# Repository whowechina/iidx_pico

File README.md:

# IIDX Pico - Beatmania IIDX Style Mini Controller
[点这里可以切换到中文版](README_CN.md)

## Features
* Cool thin design.
* Many variants: IIDX Pico, IIDX Teeny, IIDX Jumbo and IIDX Itsy.
* Foldable with soft hinge.
* Now supports both Hall effect switches and mechanical switches.
* Customizable lights and effects.
* HID lights.
* IIDX Visa card holder.
* All source files open.

## Change Notes
* All IIDX Pico variants have been integrated into this repository for better management.
* The old IIDX Teeny repository has been archived and will be no longer updated.
* Old files have been moved to the Gen1Archive directory, but can also be found in the historical versions.

## Thanks
Thanks to many respectful guys/companies who made their tools or materials free or open source (KiCad, OnShape, InkScape, Raspberry things).

Special thanks to community projects and developers.
And also these projects:
* RP_Silicon_KiCad: https://github.com/HeadBoffin/RP_Silicon_KiCad
* Type-C: https://github.com/ai03-2725/Type-C.pretty
* Bluetooth for UM: https://github.com/987123879113/Esp32EntryModel

## My Other Projects
You can check out my other cool projects.

* Popn Pico: https://github.com/whowechina/popn_pico
* IIDX Pico: https://github.com/whowechina/iidx_pico
* Chu Pico: https://github.com/whowechina/chu_pico
* Mai Pico: https://github.com/whowechina/mai_pico
* Diva Pico: https://github.com/whowechina/diva_pico
* AIC Pico: https://github.com/whowechina/aic_pico
* Groove Pico: https://github.com/whowechina/groove_pico
* Geki Pico: https://github.com/whowechina/geki_pico
* Musec Pico: https://github.com/whowechina/musec_pico
* Ju Pico: https://github.com/whowechina/ju_pico
* Bishi Pico: https://github.com/whowechina/bishi_pico
* Nos Pico: https://github.com/whowechina/nos_pico
* Voltex Pico: https://github.com/whowechina/voltex_pico
* Chord Pico: https://github.com/whowechina/chord_pico
* Dance Pico: https://github.com/whowechina/dance_pico
* Arcade Pico: https://github.com/whowechina/arcade_pico

## **Disclaimer** ##
I made this project in my personal time with no financial benefit or sponsorship. I will continue to improve the project. I have done my best to ensure that everything is accurate and functional, there's always a chance that mistakes may occur. I cannot be held responsible for any loss of your time or money that may result from using this open source project. Thank you for your understanding.

## About the License
It's CC-NC. So DIY for yourself and for your friend, don't make money from it. And plagiarism that doesn’t even dare to mention the original author is not acceptable. Please note that pooling orders and group buying for raw materials is acceptable.Selling any leftover components at cost (without profit) is also acceptable.

If you're interested in buying from me, or for commercial use, please contact me (Discord, QQ group, Goofish).
* My Discord Invitation: https://discord.gg/M8f2PPQFEA
* QQ Group: 854535476
* Goofish: whowe12345

## HOW TO BUILD
### Turntable Materials
* 1x 5mm\*2mm magnet (must be radially magnetized).
* 1x 61804-2RS deep groove ball bearing (20x32x7mm), just choose the cheaper ones.
* 2x 6705-2RS (alternative) deep groove ball bearings (25x32x4mm) for IIDX Jumbo, less wobbling.
* 1x WS2812B LED strip. Go with ones with dense LED configurations. I recommend 80 LEDs per meter or higher for IIDX Pico and IIDX Jumbo; 120 LEDs per meter or higher for IIDX Teeny;
* 1x M2.5*6 screw and hex nut, to fix disc seat, magnet seat and bearing together.
* 4x M3*8mm screws, to fix bearing seat to the base.
* 4x M3*12mm screws, for the disc. 
* 2x M3*8mm screws and hex nuts, for the banner.
* 1x Custom cut black acrylic disc, 3mm thickness for IIDX Pico and IIDX Jumbo.
* Some 10mm non slip self-adhesive silicon pads (also for Keyboard).
* Silicone tube, inner diameter 25mm, outer diameter 27mm, serves as a hinge.
* Some soft ribbon cable with 7 wires, silicone 28AWG is recommended.
* Some acetate cloth tape helps to fix the wires.

### PCB and Keyboard Materials
* 1x Raspberry Pi Pico (or Pi Pico W if you want Bluetooth). If you're building the Itsy, use the "Supermini RP2040 Zero" module instead - it looks like the RP2040 Zero, but has components only on top side.  
  https://www.raspberrypi.com/products/raspberry-pi-pico
* 11x Kailh Choc v1 or v2 key switches, I suggest using linear switches for the 7 main buttons.  
  https://www.kailhswitch.com/mechanical-keyboard-switches/low-profile-key-switches/burnt-orange-switch.html  
  https://www.kailhswitch.com/mechanical-keyboard-switches/key-switches/kailh-low-profile-switch-choc-v2.html
* 7x Kailh 2.0U low-profile stabilizers.  
  https://chosfox.com/products/kailh-1350-choc-switch-6-25u-stabilizer-set
* 2x Panasonic EVQP1K05M square tactile switches for IIDX Pico and IIDX Jumbo.  
  https://www3.panasonic.biz/ac/e/dl/catalog/index.jsp?series_cd=3473&part_no=EVQP1K05M
* 6x Panasonic EVQP1K05M or ALPS SKPMAPE010 square tactile switches for IIDX Teeny.  
  https://www3.panasonic.biz/ac/e/dl/catalog/index.jsp?series_cd=3473&part_no=EVQP1K05M  
  https://tech.alpsalpine.com/e/products/detail/SKPMAPE010/
* 1x USB Type-C socket (918-418K2023S40001 or KH-TYPE-C-16P)
* 1x AS5600 (SOP8), MT6701CT-STD (SOP8), or TMAG5273 (SOT23-6) hall angular sensor chip. For MT6701, trim pin 8 (Z/CSN) if JP1 is not present on the PCB; for AS5600, solder bridge JP1 if it is present.
* RGB LEDs
  * IIDX Pico and IIDX Jumbo (nicer light effect version)
    * 28x WS2812B-1516 or WS2812B-2020 for main buttons, pinout should be exactly like this:  
      
    * 4x WS2812B-3528 (or WS2812B-2835), for AUX buttons.
  * IIDX Pico and IIDX Jumbo (easier soldering version)
    * 11x WS2812B-3528 (or WS2812B-2835), forget about ridiculously tiny 28x LEDs.
  * IIDX Teeny
    * 18 WS2812B-3528 (or WS2812B-2835).
* 4x 0603 5.1kohm resistors for USB and I2C.
* 6x 0603 0.1uF capacitors for IIDX Pico and IIDX Jumbo, 4x for IIDX Teeny.
* 4x Kailh low-profile keycaps for IIDX Pico and IIDX Jumbo.
* 4x M3*8mm screws and hex nuts to fix parts together.

### If you want to build Hall Effect version
* WS2812B-3528 per switch is no longer an option. Because it conflicts with the pinout.
* 1x ADG708BRUZ, 8 to 1 analog switch, in TSSOP-16 (U4).
* 1x LP5907MFX-4.5 or TPS7A2042PDBVR LDO, in SOT23-5 (U6), see next line.
* 1x LM4040 shunt voltage reference, get one with 2.0\~2.1V (for 4.2V LDO) or 2.2\~2.5V (for 4.5V LDO) reference voltage, in SOT23-3 (U5).
* 7x SS49E or compatible linear Hall Effect sensors, in SOT23-3 (H1-H7).
* 1x 10ohm resistor, 0603 (R5) and leave R6 absent.
* 1x 3.3V Zener diode, in SOD-123 or SOD-123F, such as BZT52H-C3V3 (Z1).
* 7x low profile magnetic switches, Gateron/NuPhy Jade Mini or Jade Pro Mini, Kailh Star Magnetic Mini, or compatible ones. (SW1-SW7).
* Some more 0.1uF capacitors. (All remaining capacitor positions).
* This shows the soldering for Hall Effect version.  

### Step 1 - Buy
* Main PCB  
  Just go [JLC](https://jlcpcb.com/) or some other PCB vendor you like and make the order. Make sure the board thickness is **1.2mm**, it's very important!
* Acrylic disc for IIDX Pico and IIDX Jumbo.  
  Find a vendor to cut a 3mm thick black acrylic using corresponding DXF file.  
  You can 3D print a turntable disc, but it is prone to heat deformation.

### Step 2 - 3D Print
#### Keyboard
For following prints, FDM, PLA, 0.4 nozzle, 0.2mm layer.
* Keyboard base ("Keyboard Base *.stl), PLA/PETG transparent, 2 to 3 walls.
* Keyboard panel ("Keyboard Panel.stl"), PLA/PETG transparent, 2 to 3 walls. Please render the panel art and text (height 3mm+) in black if you have multi-color printing system.

#### Turntable 
For following prints, FDM, PLA, 0.4 nozzle, 0.2mm layer, 3 to 4 walls.
* Base ("Turntable \* - Base.stl"), 20-40% infill.
* Bearing seat ("Turntable - Bearing Seat"), 40% to 60% infill.
* Magnet seat ("Turntable - Magnet Seat"), 40% to 60% infill.
* Disc seat ("Turntable - Disc Seat"), 40% to 60% infill.
* For IIDX Teeny only, the disc ("Turntable Teeny - Disc"), 80%+ infill, use a textured PEI bed and concentric pattern for a better surface.
* Banner ("Turntable * - Banner"), 20-40% infill. You can render the text in black if you have multi-color printing system.
* NOTE: IIDX Jumbo with 2 bearings is abbreviated as "Jumbo 2B" in the file name.

#### Button keycaps
* Keycap ("Keycap *.stl", choose the one matches your build), resin printing is recommended, but FDM can work in a pinch.

### Step 3 - Soldering and Assembly Tips
* Keyboard
  * It's very easy to miss two USB pins of the Raspberry Pico Pi, it's at the other side. It's difficult to solder as you may leave air bubbles in the soldering hole. Trick is to use sharpest iron tip, slowly apply solder wire.  
    
  * As long as you have Pi Pico soldered, you can upload firmware and test the board. Please test frequently during the soldering and assembly process.
  * There are two small sensor boards on the main PCB, one for AS5600, the other for TMAG5273. You only need one. After a successful test, you can snap it off for turntable assembly.
  * This gamepad test page can be used for testing. You can move a screwdriver bit on top of the AS5600 or TMAG5273 to see the axis movement.  
    https://greggman.github.io/html5-gamepad-test/
  * Install the low-profile stabilizers.  
    https://docs.keeb.io/choc-stabs  
    A little trick here. Since the PCB footprint is made to support both choc v1 and v2, that leaves some wobble space for choc v1 and making alignment more difficult. So leave the key switch unsoldered, when the stabilizer, the key switch and the keycap are all in place, push the keycap down and then solder the key switch. This way the key switch will be aligned to the stabilizers better.

* Turntable
  * Assembly is pretty straightforward.  

  * Sensor board is stuck to the base using some thin double-sided tape.
  * For IIDX Jumbo, two 6705-2RS bearings are stacked together.
  * Bearings are originally with very low friction, if you need more resistance, you can add some medium viscosity damping grease, but don't add too much. "2RS" in the bearing model means it's rubber sealed, it's easy to open the rubber seal and add grease.
  * RGB LED strip is stuck to the circular LED wall, both winding directions work.  
  * The 7-wire ribbon cable is for both the RGB LED and the sensor board, 3 for RGB LED, 4 for the sensor board.  
    
  * Silicone tube is to connect the turntable and the keyboard. Ribbon cable needs to go through the tube. You need a 7mm or 8mm hole punch to make holes on the silicone tube, to match the hooks at both turntable base and the keyboard sides.

### Notes on Hall Effect version
* For Kailh Star Mini, you need to use 704 RTV silicone adhesive to secure the magnetic switch to the PCB, to prevent it wobbling.
* Calibration must be done in the command line interface.
* Travel distance for triggering and reset can be configured only in the command line interface. They're stored in profile, which means, you can switch between different profiles and have different triggering settings for each profile.

### Firmware
* The UF2 file is in the `Production\Firmware` folder. IIDX Pico/Teeny/Jumbo share the same IIDX Pico firmware.
* For the new build, hold the BOOTSEL button while connect the USB to a PC, there will be a disk named "RPI-RP2" showed up. Drag the UF2 firmware binary file into it and that's it. There's a small hole at the back side of the keyboard, it is facing right to the BOOTSEL button.
* If it is already running my IIDX firmware, hold two small AUX buttons together will do the same as the BOOTSEL button.
* You need to setup your turntable LED strip first, check the manual for the SETUP mode.
* Hold E1+E2 while powering on to start Bluetooth pairing on Pico W.
* You can set the brightness, turntable LED theme, button LED theme.
* [Nice Looking Manual Here](doc/IIDX_Pico_Manual.pdf)  

### Tools I Made
* Gamepad test - You can use it to check if all buttons and axes are working correctly.   
  https://whowechina.github.io/iidx_pico/Tools/gamepad_test.html
* Command-line tool - You can access controller's built-in CLI port using this tool.  
  https://whowechina.github.io/iidx_pico/Tools/cli_tool.html

### Bonus - IIDX Visa Card Holder

* IIDX Visa card holder is a bonus design for IIDX Pico. It can be used to hold your credit card sized arcade cards.
* Print the base and the panel, assign different color for the pattern and text on the panel. `_insert` means it's the heat-set insert version. `_flat` means it's for flat head (countersunk) screws. Transparent material is recommended.
* If you choose the `_insert` version, use 4x M1.2\*1.5mm\*2mm (thread size\*length\*diameter) heat-set inserts on base part.
* 4x M1.2\*3mm screws to fix the panel and the base together. If you choose the `_flat` version, use M1.2\*3mm flat head screws.

## CAD Source File
I'm using OnShape free subscription. It's powerful but it can't archive original designs to local, so I can only share the link here. STL/DXF/DWG files are exported from this online document.  
https://cad.onshape.com/documents/ed99bfa5b4aec5d3ea6e6ed6/w/9a87f8b714078597b4ef5e3c/e/2e27bace5a421a921473c027

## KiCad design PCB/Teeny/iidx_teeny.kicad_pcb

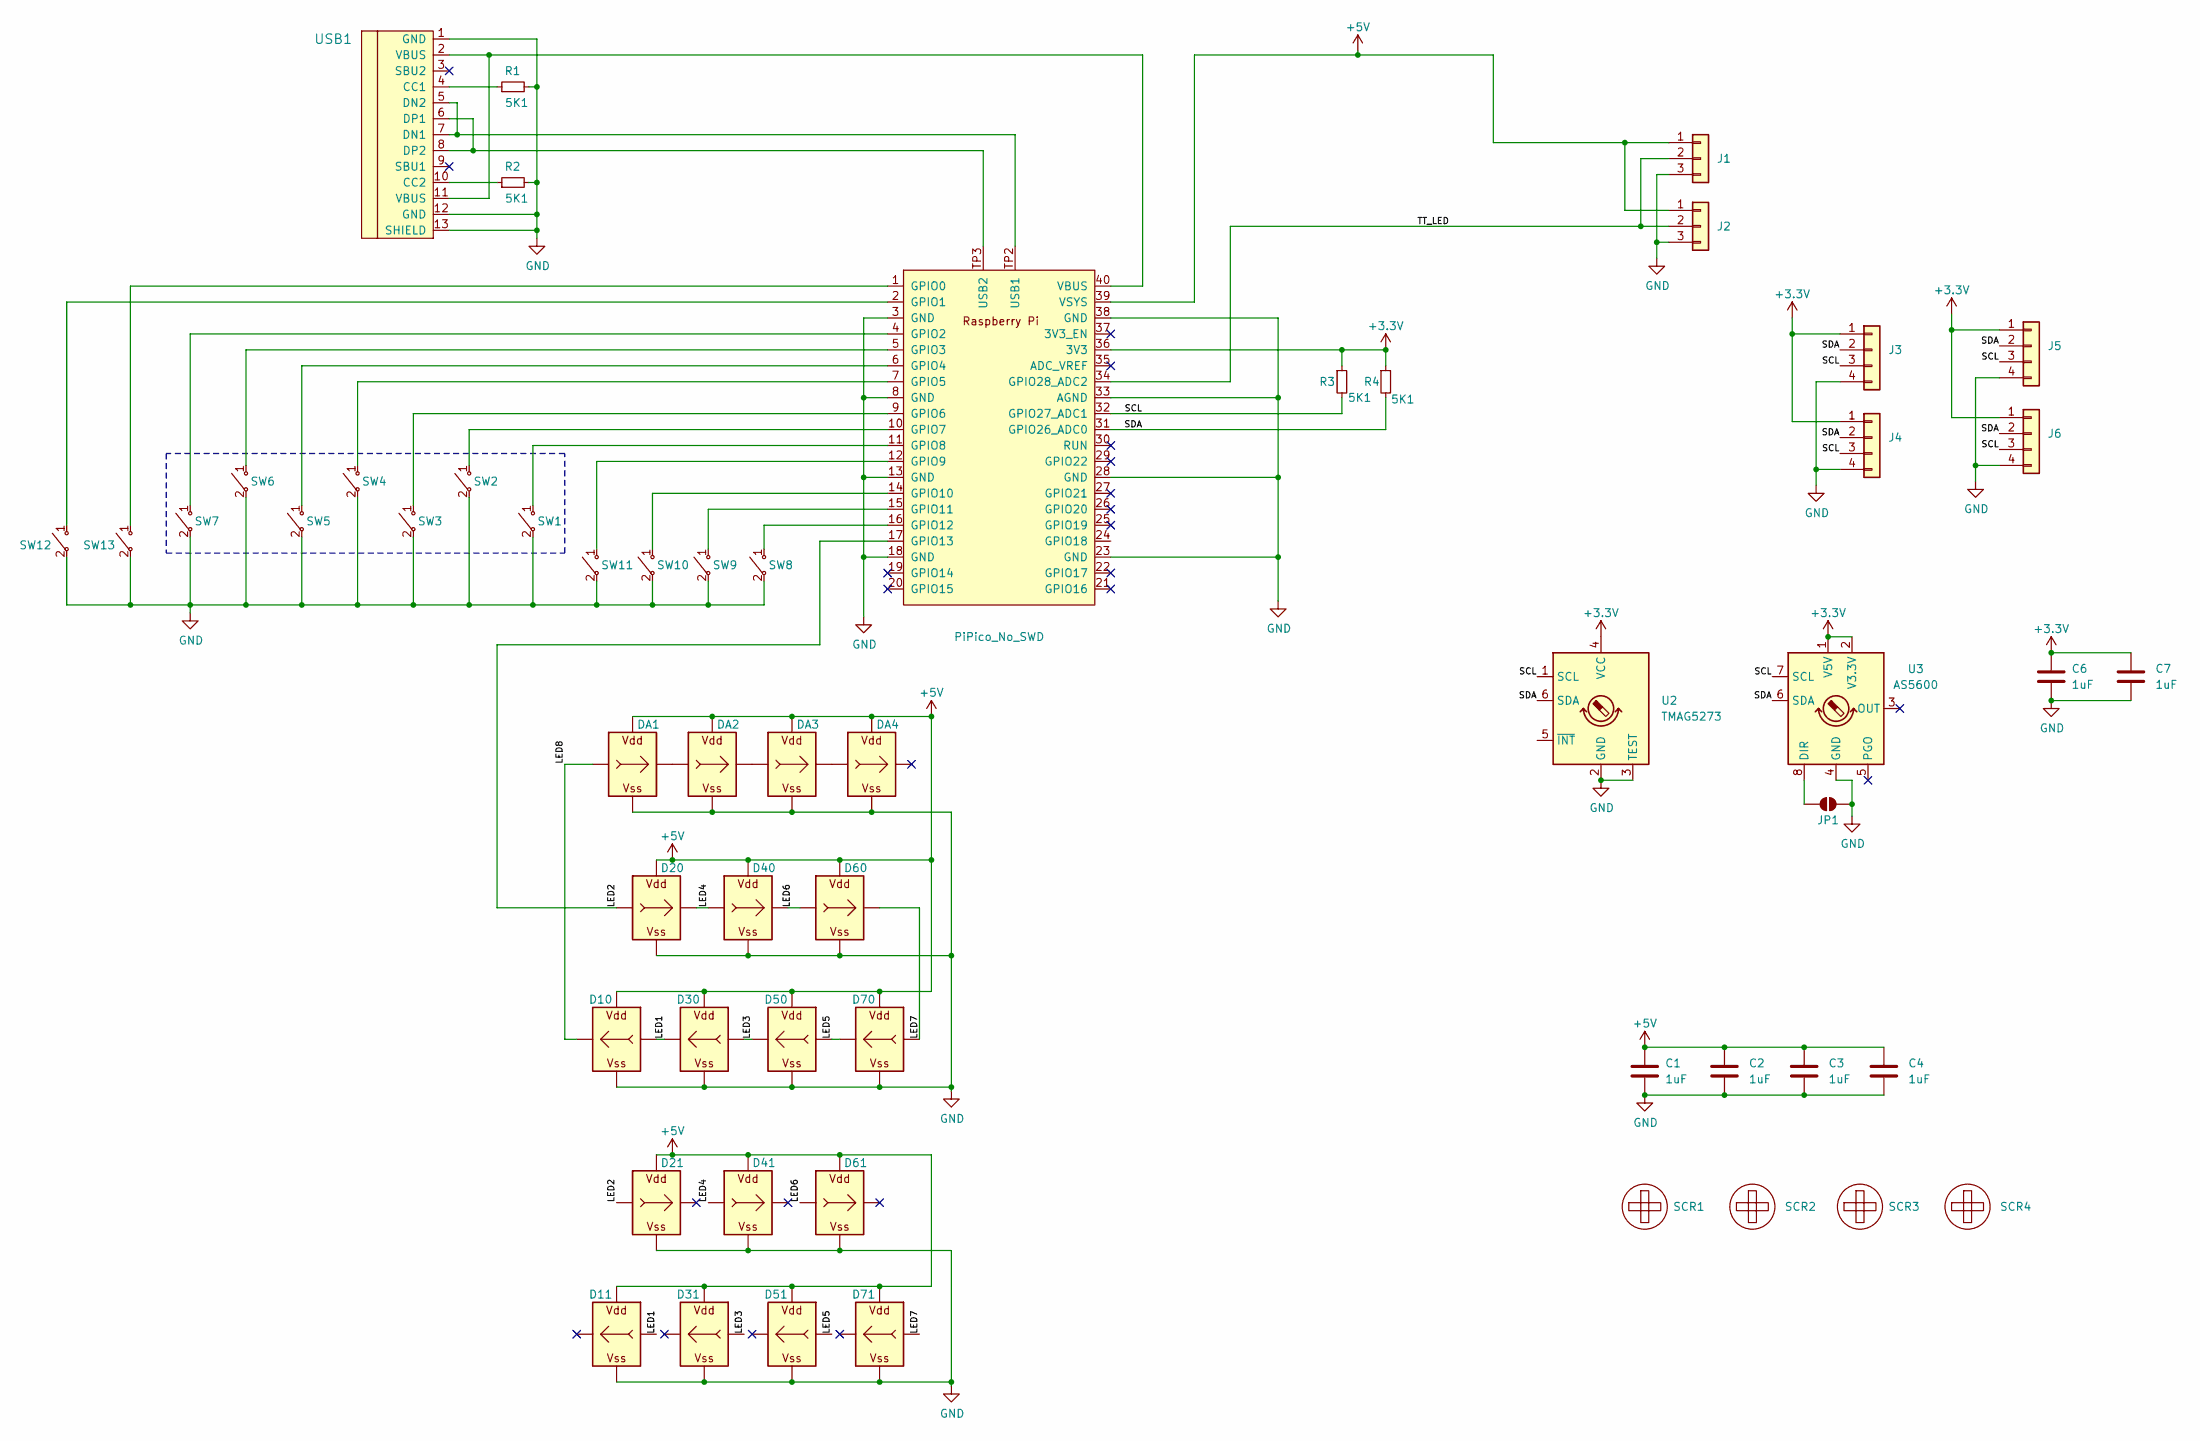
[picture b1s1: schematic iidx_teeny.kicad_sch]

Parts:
C1, C2, C3, C4, C6, C7: 1uF; C_0603_1608Metric_Pad1.08x0.95mm_HandSolder
D10, D11, D20, D21, D30, D31, D40, D41, D50, D51, D60, D61, D70, D71: WS2812B_Unified; WS2812B-2835
DA1, DA2, DA3, DA4: WS2812B_Unified; WS2812B-2835
J1, J2: RGB; SH1.0_3P_Solder_Combo
J3, J4: Spin; SH1.0_4P_Solder_Combo
J5, J6: Spin; P2.0_4P_Solder
JP1: DIR; SolderJumper-2_P1.3mm_Open_RoundedPad1.0x1.5mm
R1, R2, R3, R4: 5K1; R_0603_1608Metric_Pad0.98x0.95mm_HandSolder; LCSC C23186
SCR1, SCR2, SCR3, SCR4: ScrewHole; MountingHole_3.2mm_M3
SW1, SW2, SW3, SW4, SW5, SW6, SW7: SWITCH_SPST; SW_Kailh_Choc_V1V2_1.00u_LED
SW8, SW9, SW10, SW11, SW12, SW13: SWITCH_SPST; EVQP1K05M
U1: PiPico_No_SWD; RPi_Pico_SMD_Pins_No_SWD_No_Text
U2: TMAG5273; TSOT-23-6_HandSoldering
U3: AS5600; SOIC-8_3.9x4.9mm_P1.27mm
USB1: U262-161N-4BVC11; HRO-TYPE-C-31-M-12-Assembly; LCSC C319148

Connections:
+3.3V: C6.1, C7.1, J3.1, J4.1, J5.1, J6.1, R3.1, R4.1, U1.36 (3V3), U2.4 (VCC), U3.1 (V5V), U3.2 (V3.3V)
+5V: C1.1, C2.1, C3.1, C4.1, D10.V (VDD), D11.V (VDD), D20.V (VDD), D21.V (VDD), D30.V (VDD), D31.V (VDD), D40.V (VDD), D41.V (VDD), D50.V (VDD), D51.V (VDD), D60.V (VDD), D61.V (VDD), D70.V (VDD), D71.V (VDD), DA1.V (VDD), DA2.V (VDD), DA3.V (VDD), DA4.V (VDD), J1.1, J2.1, U1.39 (VSYS)
/LED1: D10.I (In), D11.I (In), D30.O (Out)
/LED2: D20.I (In), D21.I (In), U1.17 (GPIO13)
/LED3: D30.I (In), D31.I (In), D50.O (Out)
/LED4: D20.O (Out), D40.I (In), D41.I (In)
/LED5: D50.I (In), D51.I (In), D70.O (Out)
/LED6: D40.O (Out), D60.I (In), D61.I (In)
/LED7: D60.O (Out), D70.I (In), D71.I (In)
/LED8: D10.O (Out), DA1.I (In)
/SCL: J3.3, J4.3, J5.3, J6.3, R3.2, U1.32 (GPIO27_ADC1), U2.1 (SCL), U3.7 (SCL)
/SDA: J3.2, J4.2, J5.2, J6.2, R4.2, U1.31 (GPIO26_ADC0), U2.6 (SDA), U3.6 (SDA)
/TT_LED: J1.2, J2.2, U1.34 (GPIO28_ADC2)
GND: C1.2, C2.2, C3.2, C4.2, C6.2, C7.2, D10.G (VSS), D11.G (VSS), D20.G (VSS), D21.G (VSS), D30.G (VSS), D31.G (VSS), D40.G (VSS), D41.G (VSS), D50.G (VSS), D51.G (VSS), D60.G (VSS), D61.G (VSS), D70.G (VSS), D71.G (VSS), DA1.G (VSS), DA2.G (VSS), DA3.G (VSS), DA4.G (VSS), J1.3, J2.3, J3.4, J4.4, J5.4, J6.4, JP1.2 (B), R1.2, R2.2, SW1.2 ("~"), SW2.2 ("~"), SW3.2 ("~"), SW4.2 ("~"), SW5.2 ("~"), SW6.2 ("~"), SW7.2 ("~"), SW8.2 ("~"), SW9.2 ("~"), SW10.2 ("~"), SW11.2 ("~"), SW12.2 ("~"), SW13.2 ("~"), U1.3 (GND), U1.8 (GND), U1.13 (GND), U1.18 (GND), U1.23 (GND), U1.28 (GND), U1.33 (AGND), U1.38 (GND), U2.2 (GND), U2.3 (TEST), U3.4 (GND), USB1.1 (GND), USB1.12 (GND), USB1.13 (SHIELD)
unnamed: DA1.O (Out), DA2.I (In)
unnamed: DA2.O (Out), DA3.I (In)
unnamed: DA3.O (Out), DA4.I (In)
unnamed: JP1.1 (A), U3.8 (DIR)
unnamed: SW13.1 ("~"), U1.1 (GPIO0)
unnamed: SW12.1 ("~"), U1.2 (GPIO1)
unnamed: SW7.1 ("~"), U1.4 (GPIO2)
unnamed: SW6.1 ("~"), U1.5 (GPIO3)
unnamed: SW5.1 ("~"), U1.6 (GPIO4)
unnamed: SW4.1 ("~"), U1.7 (GPIO5)
unnamed: SW3.1 ("~"), U1.9 (GPIO6)
unnamed: SW2.1 ("~"), U1.10 (GPIO7)
unnamed: SW1.1 ("~"), U1.11 (GPIO8)
unnamed: SW11.1 ("~"), U1.12 (GPIO9)
unnamed: SW10.1 ("~"), U1.14 (GPIO10)
unnamed: SW9.1 ("~"), U1.15 (GPIO11)
unnamed: SW8.1 ("~"), U1.16 (GPIO12)
unnamed: U1.TP2 (USB1), USB1.5 (DN2), USB1.7 (DN1)
unnamed: U1.TP3 (USB2), USB1.6 (DP1), USB1.8 (DP2)
unnamed: U1.40 (VBUS), USB1.2 (VBUS), USB1.11 (VBUS)
unnamed: R1.1, USB1.4 (CC1)
unnamed: R2.1, USB1.10 (CC2)

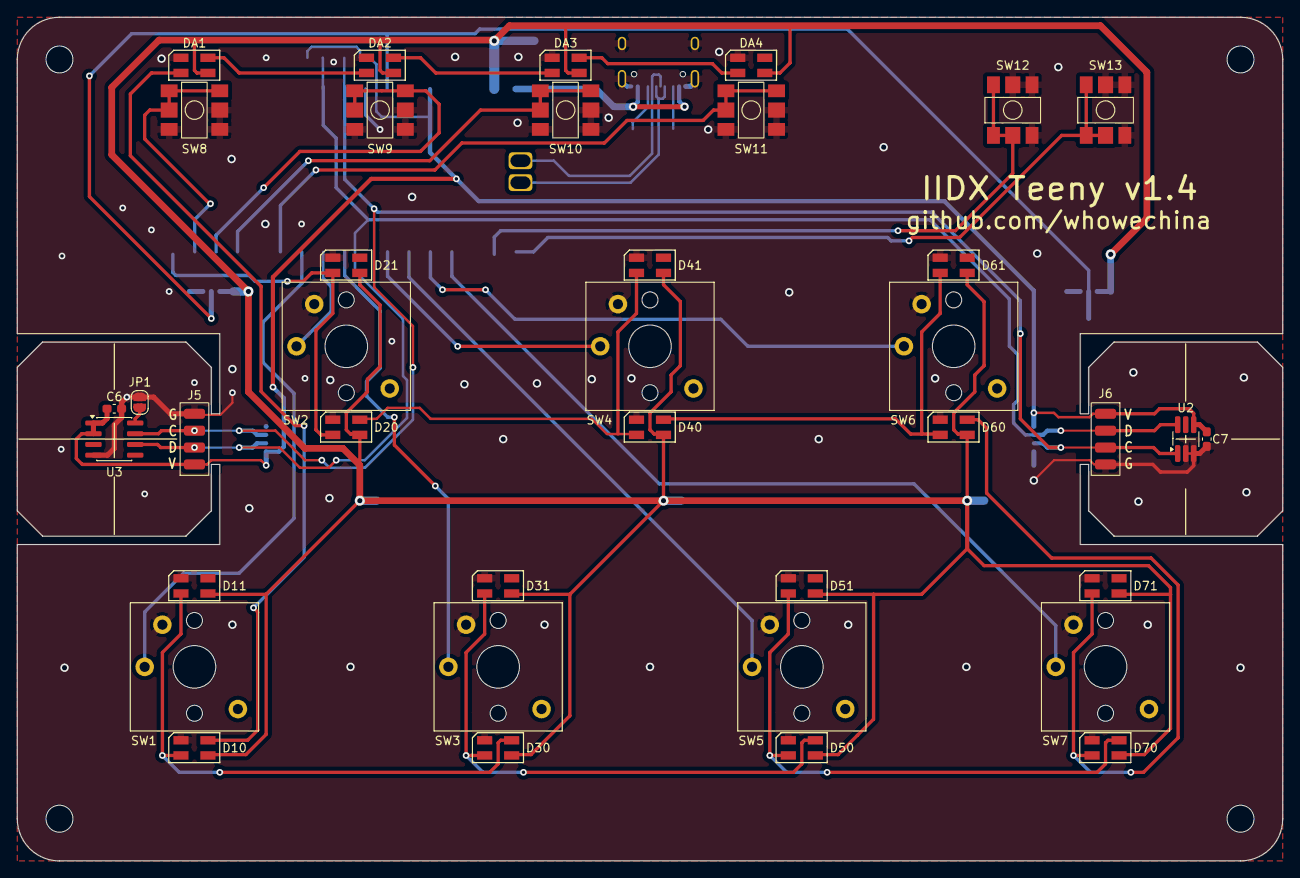
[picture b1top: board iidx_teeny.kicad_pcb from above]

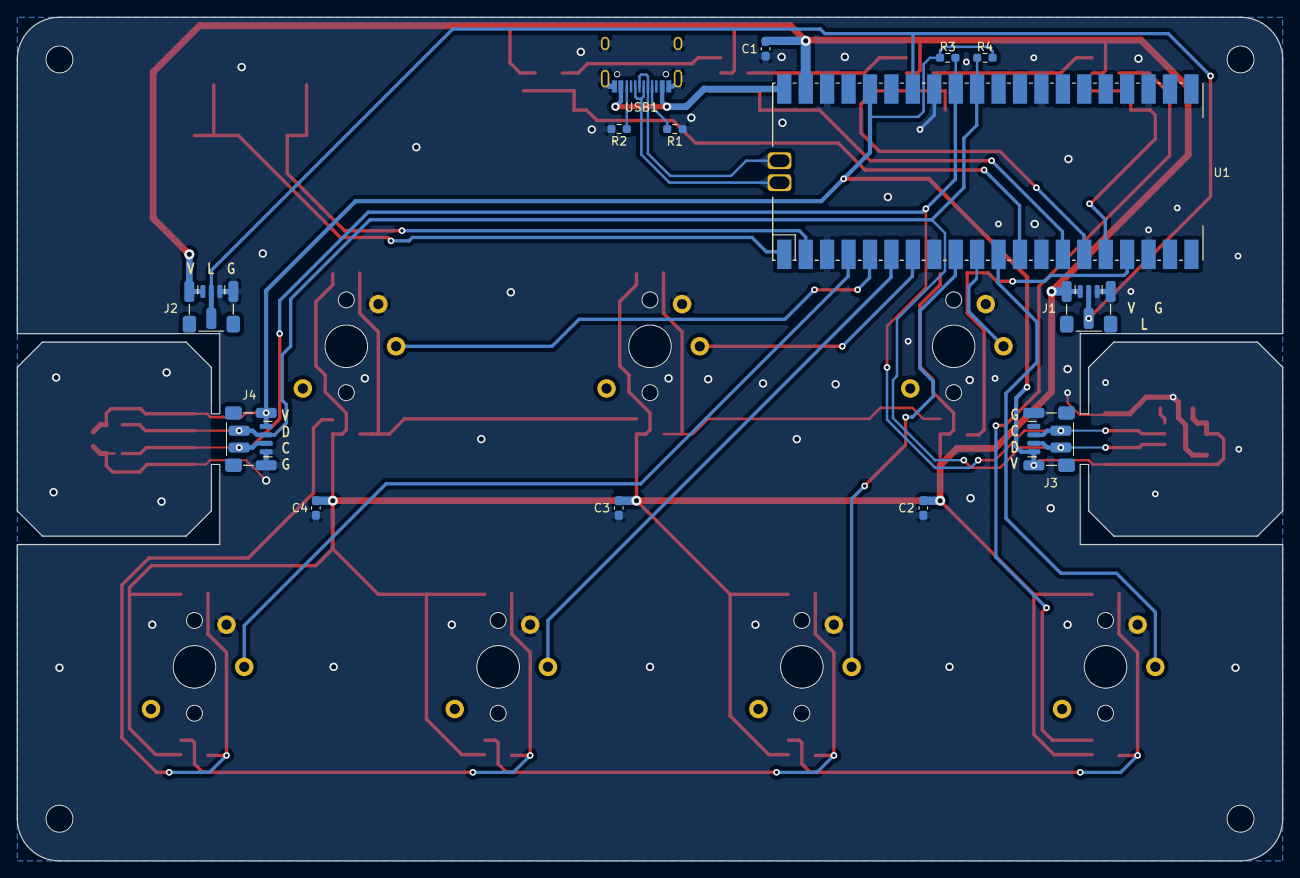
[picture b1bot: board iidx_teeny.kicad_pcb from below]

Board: 2 copper layers, 150.0 x 100.0 mm, 56 parts (14 on the bottom side), 36 nets.

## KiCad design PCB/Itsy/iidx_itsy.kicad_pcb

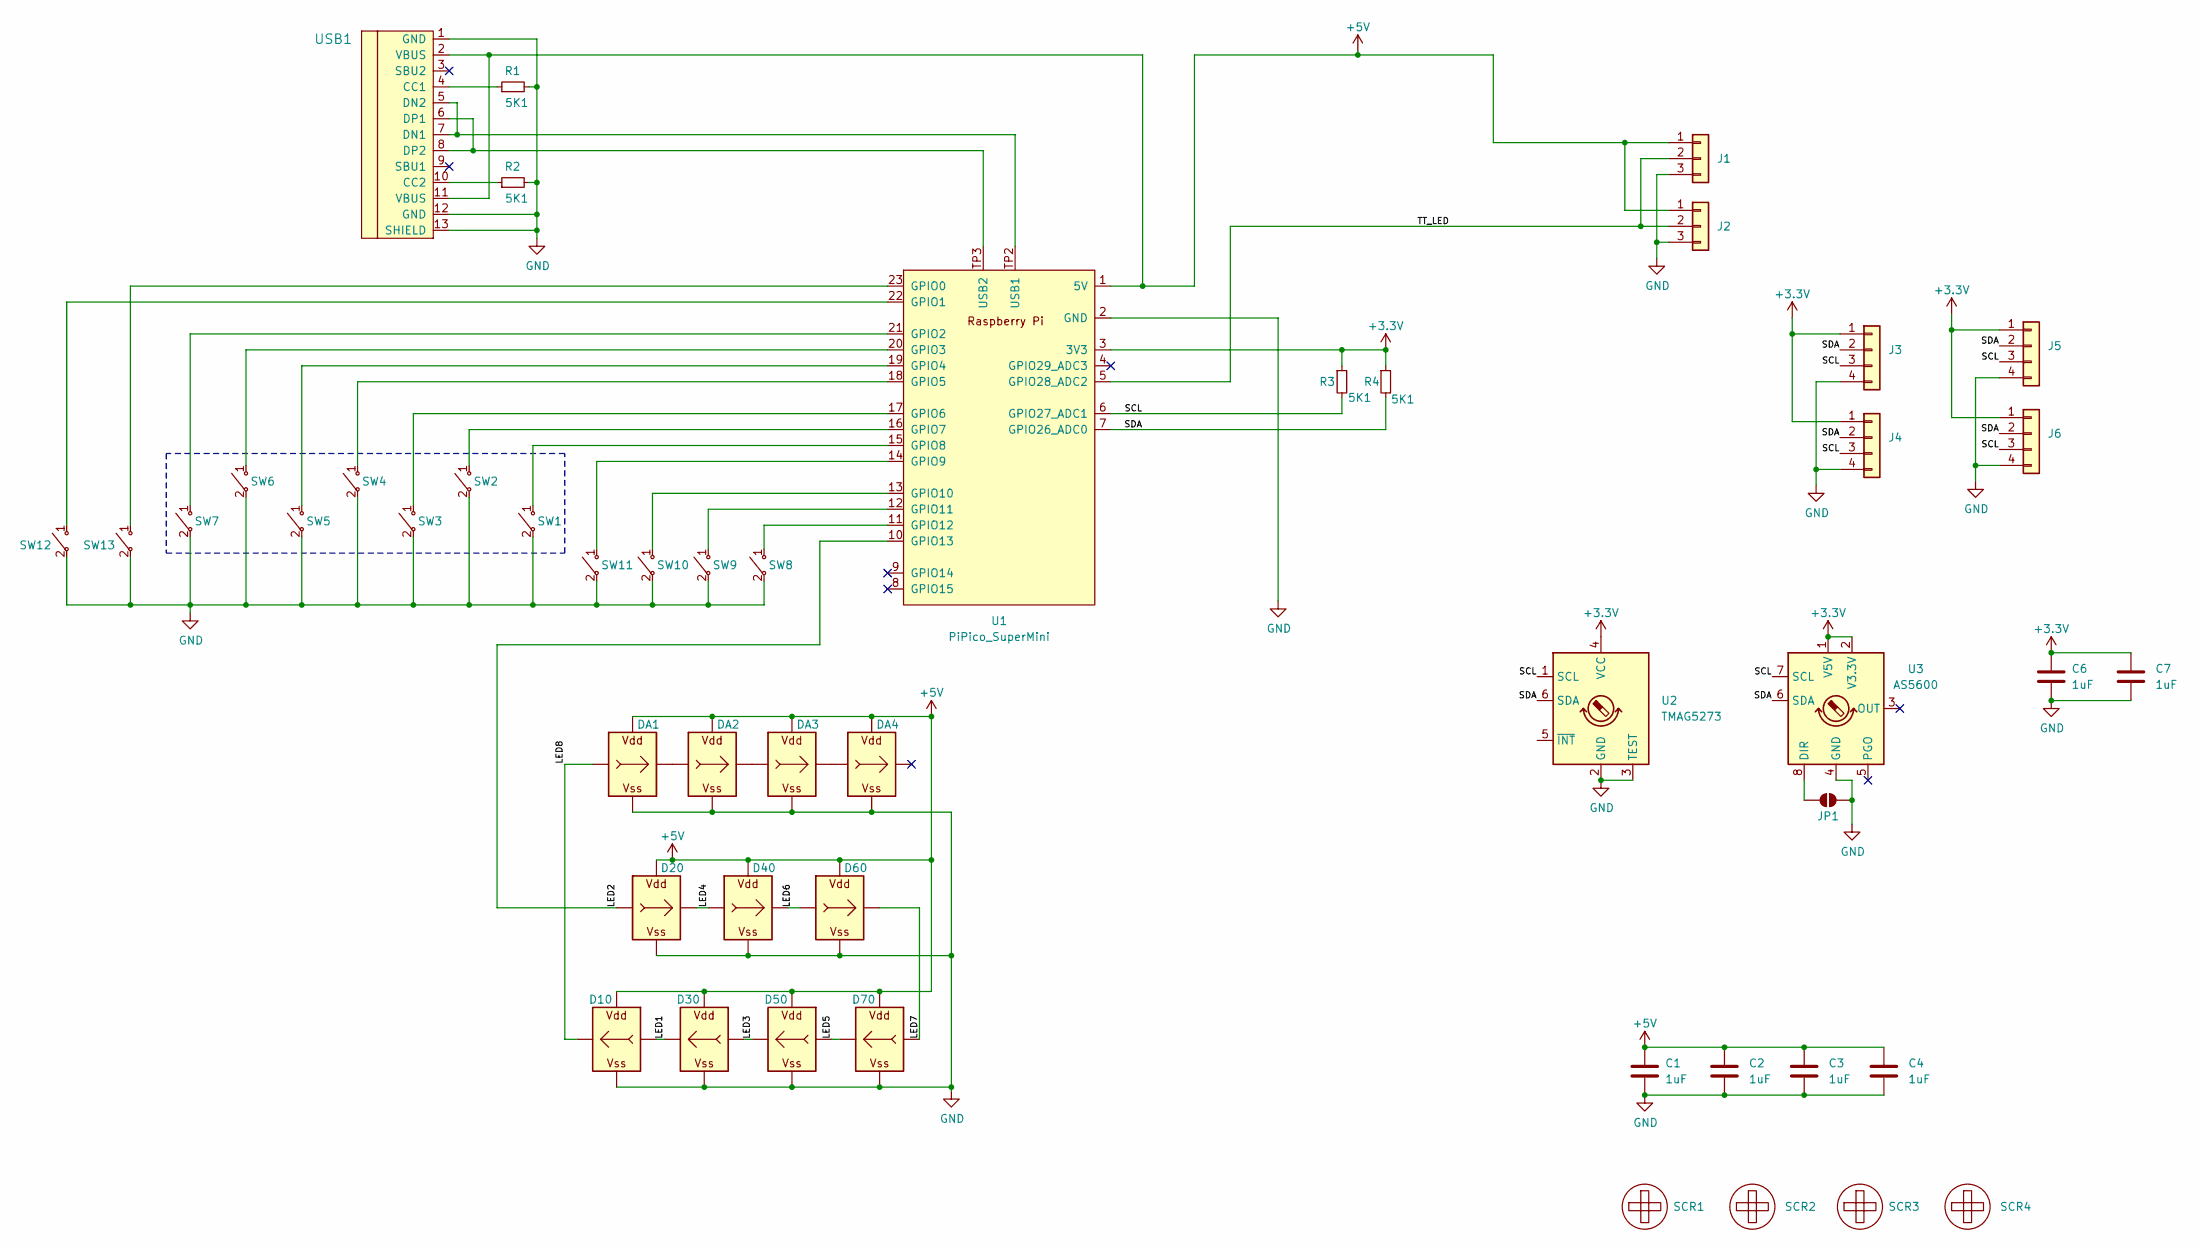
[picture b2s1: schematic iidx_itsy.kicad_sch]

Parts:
C1, C2, C3, C4, C6, C7: 1uF; C_0603_1608Metric_Pad1.08x0.95mm_HandSolder
D10, D20, D30, D40, D50, D60, D70: WS2812B_Unified; WS2812B-2835
DA1, DA2, DA3, DA4: WS2812B_Unified; WS2812B-2835
J1, J2: RGB; P1.8_3P_Solder
J3, J4, J5, J6: Spin; P1.8_4P_Solder
JP1: DIR; SolderJumper-2_P1.3mm_Open_RoundedPad1.0x1.5mm
R1, R2, R3, R4: 5K1; R_0603_1608Metric_Pad0.98x0.95mm_HandSolder; LCSC C23186
SCR1, SCR2, SCR3, SCR4: ScrewHole; MountingHole_3.2mm_M3
SW1, SW2, SW3, SW4, SW5, SW6, SW7: SWITCH_SPST; SW_Kailh_Choc_V1V2_1.00u_LED
SW8, SW9, SW10, SW11, SW12, SW13: SWITCH_SPST; EVQP1K05M
U1: PiPico_SuperMini; RPi_Pico_SuperMini
U2: TMAG5273; TSOT-23-6_HandSoldering
U3: AS5600; SOIC-8_3.9x4.9mm_P1.27mm
USB1: U262-161N-4BVC11; HRO-TYPE-C-31-M-12-Assembly; LCSC C319148

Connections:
+3.3V: C6.1, C7.1, J3.1, J4.1, J5.1, J6.1, R3.1, R4.1, U1.3 (3V3), U2.4 (VCC), U3.1 (V5V), U3.2 (V3.3V)
+5V: C1.1, C2.1, C3.1, C4.1, D10.V (VDD), D20.V (VDD), D30.V (VDD), D40.V (VDD), D50.V (VDD), D60.V (VDD), D70.V (VDD), DA1.V (VDD), DA2.V (VDD), DA3.V (VDD), DA4.V (VDD), J1.1, J2.1, U1.1 (5V), USB1.2 (VBUS), USB1.11 (VBUS)
/LED1: D10.I (In), D30.O (Out)
/LED2: D20.I (In), U1.10 (GPIO13)
/LED3: D30.I (In), D50.O (Out)
/LED4: D20.O (Out), D40.I (In)
/LED5: D50.I (In), D70.O (Out)
/LED6: D40.O (Out), D60.I (In)
/LED7: D60.O (Out), D70.I (In)
/LED8: D10.O (Out), DA1.I (In)
/SCL: J3.3, J4.3, J5.3, J6.3, R3.2, U1.6 (GPIO27_ADC1), U2.1 (SCL), U3.7 (SCL)
/SDA: J3.2, J4.2, J5.2, J6.2, R4.2, U1.7 (GPIO26_ADC0), U2.6 (SDA), U3.6 (SDA)
/TT_LED: J1.2, J2.2, U1.5 (GPIO28_ADC2)
GND: C1.2, C2.2, C3.2, C4.2, C6.2, C7.2, D10.G (VSS), D20.G (VSS), D30.G (VSS), D40.G (VSS), D50.G (VSS), D60.G (VSS), D70.G (VSS), DA1.G (VSS), DA2.G (VSS), DA3.G (VSS), DA4.G (VSS), J1.3, J2.3, J3.4, J4.4, J5.4, J6.4, JP1.2 (B), R1.2, R2.2, SW1.2 ("~"), SW2.2 ("~"), SW3.2 ("~"), SW4.2 ("~"), SW5.2 ("~"), SW6.2 ("~"), SW7.2 ("~"), SW8.2 ("~"), SW9.2 ("~"), SW10.2 ("~"), SW11.2 ("~"), SW12.2 ("~"), SW13.2 ("~"), U1.2 (GND), U2.2 (GND), U2.3 (TEST), U3.4 (GND), USB1.1 (GND), USB1.12 (GND), USB1.13 (SHIELD)
unnamed: DA1.O (Out), DA2.I (In)
unnamed: DA2.O (Out), DA3.I (In)
unnamed: DA3.O (Out), DA4.I (In)
unnamed: JP1.1 (A), U3.8 (DIR)
unnamed: SW13.1 ("~"), U1.23 (GPIO0)
unnamed: SW12.1 ("~"), U1.22 (GPIO1)
unnamed: SW7.1 ("~"), U1.21 (GPIO2)
unnamed: SW6.1 ("~"), U1.20 (GPIO3)
unnamed: SW5.1 ("~"), U1.19 (GPIO4)
unnamed: SW4.1 ("~"), U1.18 (GPIO5)
unnamed: SW3.1 ("~"), U1.17 (GPIO6)
unnamed: SW2.1 ("~"), U1.16 (GPIO7)
unnamed: SW1.1 ("~"), U1.15 (GPIO8)
unnamed: SW11.1 ("~"), U1.14 (GPIO9)
unnamed: SW10.1 ("~"), U1.13 (GPIO10)
unnamed: SW9.1 ("~"), U1.12 (GPIO11)
unnamed: SW8.1 ("~"), U1.11 (GPIO12)
unnamed: U1.TP2 (USB1), USB1.5 (DN2), USB1.7 (DN1)
unnamed: U1.TP3 (USB2), USB1.6 (DP1), USB1.8 (DP2)
unnamed: R1.1, USB1.4 (CC1)
unnamed: R2.1, USB1.10 (CC2)

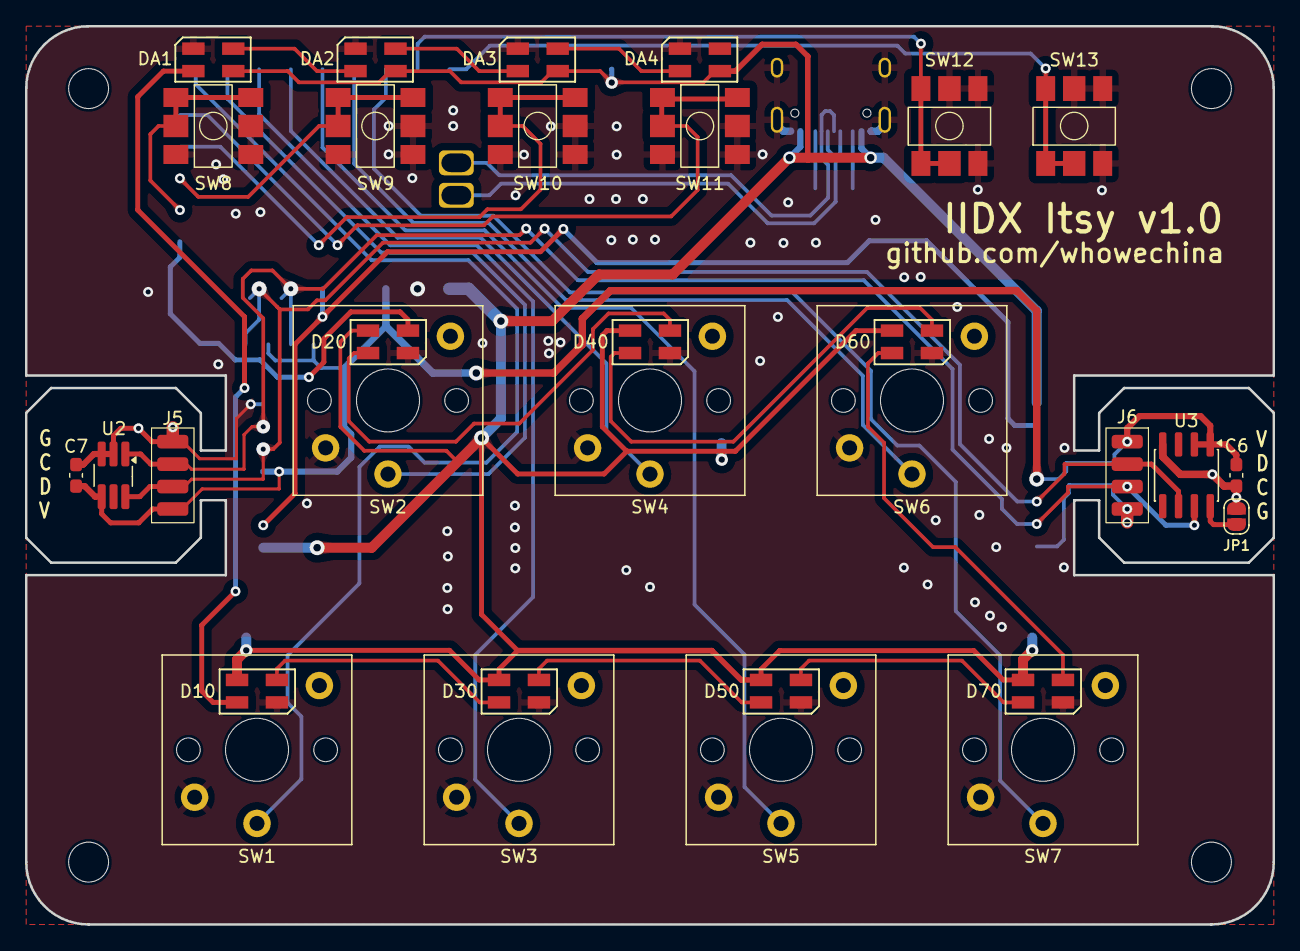
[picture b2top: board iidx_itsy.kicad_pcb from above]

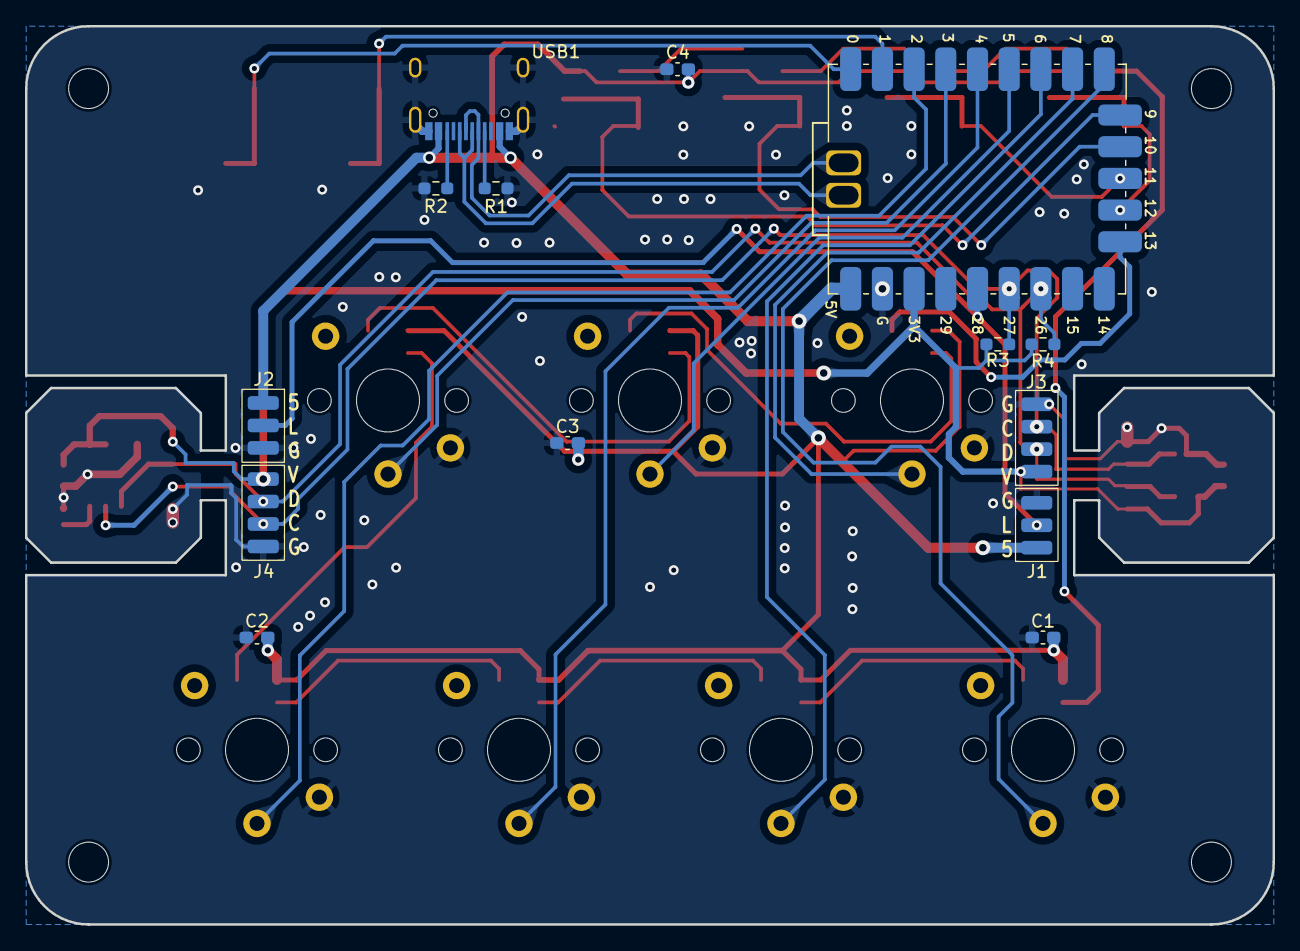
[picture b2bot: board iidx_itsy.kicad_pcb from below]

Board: 2 copper layers, 100.0 x 72.0 mm, 49 parts (14 on the bottom side), 35 nets.

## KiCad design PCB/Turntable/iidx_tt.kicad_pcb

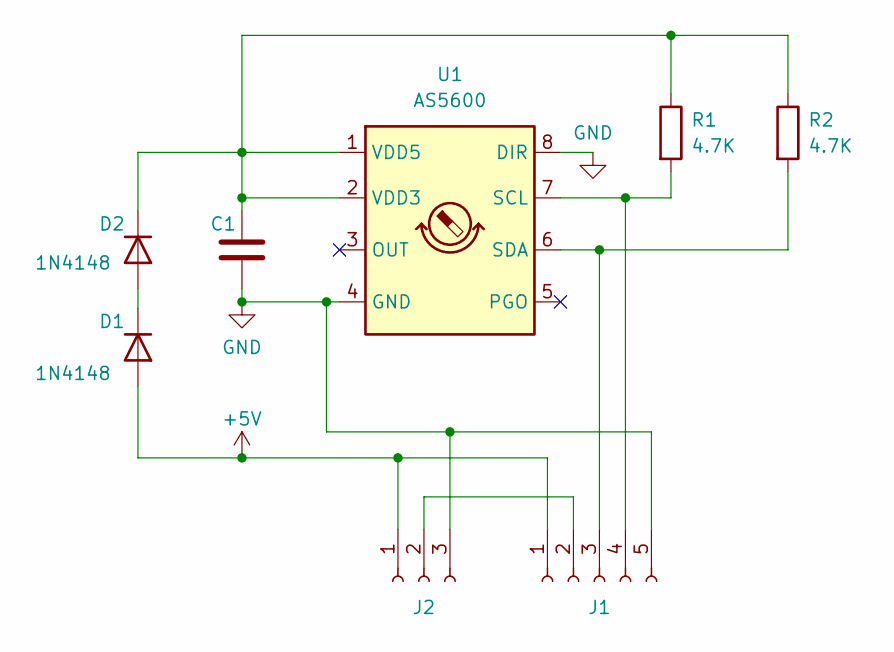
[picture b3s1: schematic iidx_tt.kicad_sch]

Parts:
C1: C; C_0603_1608Metric
D1, D2: 1N4148; D_SOD-123
J1: Conn_01x05_Female; Pads5
J2: Conn_01x03_Female; Pads3
R1, R2: 4.7K; R_0603_1608Metric
U1: AS5600; SOIC-8_3.9x4.9mm_P1.27mm

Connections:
+5V: D1.2 (A), J1.1, J2.1
GND: C1.2, J1.5, J2.3, U1.4 (GND), U1.8 (DIR)
unnamed: C1.1, D2.1 (K), R1.1, R2.1, U1.1 (VDD5), U1.2 (VDD3)
unnamed: D1.1 (K), D2.2 (A)
unnamed: J1.2, J2.2
unnamed: J1.4, R1.2, U1.7 (SCL)
unnamed: J1.3, R2.2, U1.6 (SDA)

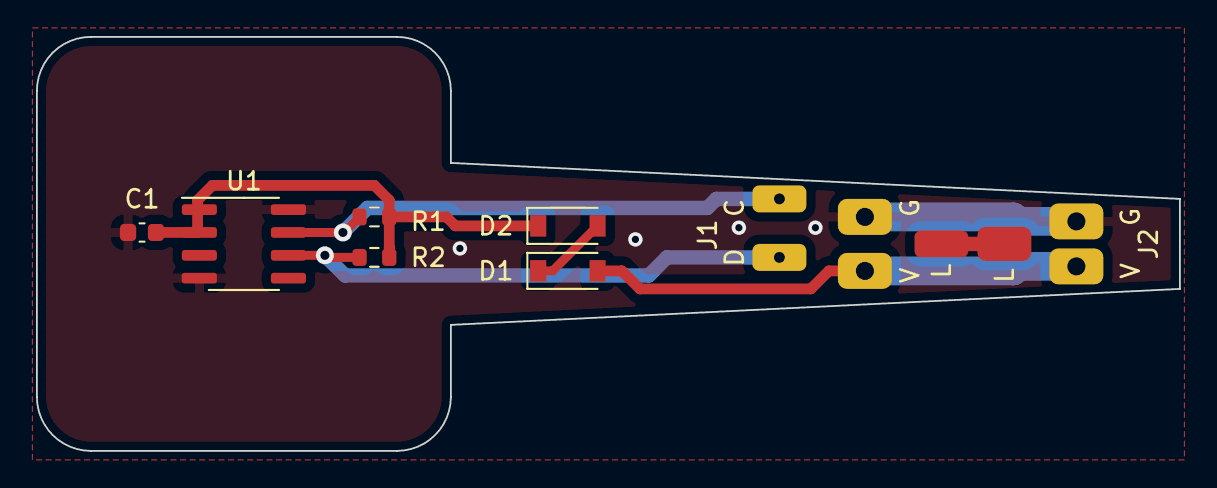
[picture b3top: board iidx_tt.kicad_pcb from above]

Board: 2 copper layers, 63.5 x 23.0 mm, 8 parts (0 on the bottom side), 7 nets.

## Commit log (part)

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2023-04-01 Migrate to iidx_pico public repo
2023-04-01 Readme started.
2023-04-01 Update readme with effect video
2023-04-01 Materials part in README
2023-04-01 Minor updates.
2023-04-01 More updates.
2023-04-02 Better numbers on TTshaft
2023-04-02 Easier to define a magnet in TTshaft
2023-04-02 Better numbers for bearing seat
2023-04-02 Created PCB for turntable
2023-04-02 Ignore backups for git
2023-04-02 Update turntable PCB
2023-04-02 Turntable gerber added
2023-04-02 Production categorization
2023-04-02 Some progress in README
2023-04-04 Some progress
2023-04-05 Turntable hotswap
2023-04-05 Corrected some comment
2023-04-05 Just begin the "Setup" feature
2023-04-05 Defined live settings.
2023-04-06 3.3 to 5 level shifter added to PCB
2023-04-06 Some README updates.
2023-04-07 Adds 3.5mm 4P jack connection option
2023-04-08 PCB bottom supports headphone jack
2023-04-08 Small updates on README
2023-04-08 PCB finetune a little bit
2023-04-08 Updates on README
2023-04-08 Big update on firmware
2023-04-09 Dynamic LED setup working
2023-04-09 HSV color working
2023-04-09 AS5600 analog support
2023-04-11 Update Readme for keyboard soldering
2023-04-11 Add TVS diode and filter capacitor to PCB
2023-04-14 I2C to 333KHz for higher reliability.
2023-04-15 Document update mainly on turntable
2023-04-15 Document update on solder part
2023-04-16 Analog and I2C mode change at runtime
2023-04-16 Document update again.
2023-04-16 Resistors to bypass level shifter
2023-04-16 Firmware manual pptx early version
2023-04-16 Hope better inteference resistance
2023-04-16 ADC auto adjust and analog deadzone
2023-04-18 Small update to Readme
2023-04-18 Add LED Off mode
2023-04-19 Update readme with 5-wire cable solution
2023-04-19 Update Readme on analog part
2023-04-19 Better setup mode
2023-04-19 Update Readme on turntable LED
2023-04-21 Choice for alternative I2C pins
2023-04-21 Analog wiring updated
2023-04-21 Effect mode working
2023-04-22 Effect mode quickset
2023-04-22 Keycap print FDM guide
2023-04-22 Choc V2 FDM option optimized
2023-04-29 Larger PCB bottom pads
2023-04-29 Key color setting done
2023-04-30 TT led as key color setting indicator
2023-04-30 Key theme selection
2023-04-30 Another update on README
2023-04-30 TT theme setup
2023-05-03 Turntable ppr setting
2023-05-03 Firmware binary for ppr setting
2023-05-15 Konami spoof mode support.
2023-05-16 Little update on README
2023-05-21 Put license file
2023-05-26 Fix a small LED flashing bug
2023-05-28 Brightness level and start work on bluetooth
2023-05-28 Better sensor default value
2023-06-04 Start to work on bluetooth
2023-07-23 Keyboard side hinge solution
2023-07-23 Turntable side hinge solution
2023-08-06 Give up on Bluetooth
2023-08-06 Option for hinge (fixed connection)
2023-08-30 Give up BLE and fix UF2 firmware
2023-09-16 Fixed a major config save bug
2023-10-02 Readme update
2023-10-05 Bearing seat for hinge version
2023-10-05 New flash magic to get rid of old corrupted data
2023-10-14 Crossreference to mai pico
2023-11-12 Some markdown errors fixed
2023-12-03 Readme update with hinge option
2023-12-10 Big update (analog and effect mode removed)
2023-12-10 Manual gif in README
2024-01-03 Removal of confusion parts in PCB
2024-04-30 Fix string issue in USB desc
2024-06-08 Turntable noise filtering and debouncing
2024-06-08 Add TT hid lights
    Add TT hid lights mode
2024-06-10 Refactoring "HID lights for turntable"
2024-09-05 Thanks to some projects
2024-09-09 PCB v1.3 fixes key "sticky-feel" problem
2024-09-09 Simple fix for earlier PCB versions.
2024-10-02 License part in README
2024-10-02 Cross-reference update
2024-10-18 Cross-reference and Discord invitation
2024-11-20 PCB v1.4 (sensor on board)
2024-12-03 Supports TMAG5273 sensor
2024-12-03 CAD Artworks
2024-12-06 PCB v1.41 (better 1615 LED footprint)
2024-12-12 Archive the old design
2024-12-12 Refactored 3DPrint files
2024-12-12 Re-arrange 3DPrint files
2024-12-13 Readme in progress
2024-12-19 Remove deadzone setting
2024-12-19 Live view in tt theme setting
2024-12-19 Remove deadzone in old manual
2024-12-19 Remove backup files
2024-12-19 TT theme options
2024-12-19 Add missing Bearing Seat
2024-12-19 Center piece art
2024-12-19 Minor improvements
2024-12-20 Fix not reporting button bug
2024-12-20 Change default button color
2024-12-21 Use hex nut to fix disc seat and magnet seat
2024-12-22 Prepare for more tt theme
2025-01-04 Better polling rate
2025-01-07 Minor refactoring
2025-01-09 Pico PCB v1.42 for lenient stabilizer cut
2025-01-09 Quick fix of Pico PCB v1.42
2025-01-11 Turntable STL finetune
2025-01-15 Update missing teeny disc
2025-01-16 Teeny PCB v1.31, finetune
2025-01-16 Ignore build files
2025-01-16 Latest finetuned STL files
2025-01-19 Reduce report jitter
2025-01-19 New TT theme in progress
2025-02-06 Jumbo Banner 1P and 2P
2025-02-09 Better pads and naming
2025-02-09 PCB tolerance
2025-02-09 Append previous PCB tolerance commit
2025-02-21 Sensor board tolerance for TT base
2025-02-22 Reinforce the bearing seat screws on base
2025-02-23 Guide for new gen (eng first)
2025-02-23 Upload missing images in doc
2025-02-24 CN version guide done
2025-02-24 3D print files for Jumbo and Pico discs
2025-02-27 Update hole punch size
2025-03-05 Save supports larger data
2025-03-05 Fix save page issue
2025-03-05 Refactoring for config and rgb led and level
2025-03-06 RGB order and improve setup experience
2025-03-06 Profile based config
2025-03-06 Profile fully working
2025-03-06 UF2 for profile support
2025-03-07 Some refactoring of rgb
2025-03-07 Color format translation right before drive led
2025-03-07 Cenrtralize level and gamma mix
2025-03-07 Effects no direct dependency on config
2025-03-07 UF2 contains latest changes
2025-03-07 Better naming (effect -> style)
2025-03-07 Rename save to savedata
2025-03-10 Update manual
2025-03-11 Update and finetune manual
2025-04-04 Cross-reference to new projects
2025-04-23 More debouncing
2025-04-26 Periodic HID report
2025-05-03 Granular ppr setting
2025-05-09 Fix links to manual
2025-05-15 Keydown statistics
2025-05-15 CLI welcome and build time
2025-05-21 USB descriptor cleanup
2025-05-21 LR2 mode in sensor setup
2025-06-20 Manual update (also CN version)
2025-06-21 12bit turntable
2025-08-09 Skip B8 on komani spoof mode
2025-08-15 Alternative I2C port for the sensor
2025-08-15 Hall effect button support
2025-08-16 Revert to 8bit turntable
2025-08-16 Hall defaults and reserve bytes
2025-08-16 UF2 for hall support and 8bit turntable
2025-08-16 Unique sn in usb dsc
2025-08-16 Hall effect switch support
2025-09-02 Pico PCB v1.52, clearance for stab steel
2025-09-23 Name change, hall_version to new_board
2025-09-23 Cross-reference and typo fixes
2025-09-27 Keycaps optimized
2025-09-27 Live trigger distance setting
2025-09-27 Better Hall defaults
2025-09-27 Fix live trigger setting issue
2025-10-09 Clarify on LDO and reference option
2025-10-15 Manual in Korean
2025-10-27 Displays sensor status in console
2025-10-27 Fix HID descriptor issue (thanks to yppy)
2025-10-27 Fix firmware timestamp
2025-11-17 Finetune cable teeth and banner edge
2025-11-25 Hall button lights
2025-11-30 Fix E1 button lights
2025-12-02 Explicitly mentioning 2.0U stabs
2025-12-04 Fix HID axis direction
2025-12-10 Gamepad test tool
2025-12-10 Minor text fix
2025-12-10 Finetune the gamepad test tool
2025-12-10 Finetune gamepad test tool
2025-12-12 PCB Pico v1.53 (vref from vbus)
2025-12-18 Higher hall detect threshold
2025-12-18 Hall-suppress for some faulty pico
2025-12-19 Command line tool page
2025-12-19 Improve gamepad display
2025-12-22 Dual language toggle and HID light support
2025-12-22 Gampad test periodic HID output
2025-12-22 Fix HID light in hall LED modes
2025-12-22 gamepad_test templates for HID light panel
2025-12-22 gamepad test: Diva Pico template
2025-12-31 Limit 200 lines only.
2026-01-03 PCB 1.54 (stab steel clearance)
2026-01-03 Allow empty line and flush the "Program" message
2026-01-05 Fix Help command in CLI tool
2026-01-15 Fix safe trigger value leakage
2026-02-05 Minor visual improvement
2026-03-04 Remove width limit in gamepad test
2026-03-05 CLI tools detects disconnect
2026-03-05 Enlarge the screw holes on discs
2026-03-11 Doc reference update
2026-03-19 Minor protection/fix in savedata
2026-03-19 MT6701 support and some other fix
2026-03-19 PCB v1.6 (support MT6701)
2026-03-19 Doc update for JP1
2026-03-21 Fix usb loop when no sensors
2026-03-27 Update PCB v1.6 files missed
2026-03-31 CLI tool supports Ctrl+C
2026-04-02 Better way handling flash lockout
2026-04-11 Fix ppr description in doc
2026-04-18 Add clean save option for flash inconsistency
2026-04-19 Config versioning and factory reset at power-up
2026-04-23 HAT display in gamepad test
2026-05-07 Boot on some slow flash ram
2026-05-16 IIDX Itsy and IIDX Visa
2026-05-16 Update readme for the IIDX Visa
2026-05-17 Two print options for IIDX Visa Base
2026-05-17 CLI tool supports different prompts
2026-05-23 More panel tolerance with keycap
2026-05-23 Countersunk screw option for IIDX Visa
2026-06-13 Fix mislead info caused by markdown
2026-06-14 Mention Supermini RP2040 Zero for Itsy in the guide
